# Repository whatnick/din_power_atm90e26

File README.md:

# DIN Rail Format Energy Meter Base Board
## Power SMPS module
- 90v-240v AC input
- Isolated 5V output
- 600mA / 3W power rating

## Over-voltage protection/over-current protection
- 0.1A rated PTC fuse
- 300V rated TVS suppressors, x1 per-phase

## Isolation
- 5v DC-DC isolator to power metering module

## Power supply clean-up
- x2 1117 series LDO for generating 3.3v from 5V input to clean up SMPS noise

## Backup-power
- MCP73831 series floating Lipo battery charger for backup lipo battery

## AC Voltage Sampler
- x3 Voltage divider ladders with 880K + 1K total serial resistance

## AC current Sampler
- x8 2.4ohm current sense resistor based CT clamp inputs

## Connectors
- 5.08mm spacing phoenix contact AC voltage connector
- Molex nanofit 2x4 type dense AC current clamp connectors

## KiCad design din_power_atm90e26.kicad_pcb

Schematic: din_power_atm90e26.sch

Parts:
C1, C2, C3: 33n; C_0603
C4, C5, C6, C7, C8, C9: 1uF; C_0603
D1: D_Schottky; D_SOD-323F
D2: LED; LED_0603
F1: Polyfuse; C_Disc_D10.0mm_W2.5mm_P5.00mm
G1: LOGO; Whatnick_logo
J1: CONN_01X06; PhoenixContact_MC-G_06x5.08mm_Angled
J2: VBAT; JST_SH_BM02B-SRSS-TB_02x1.00mm_Straight
J3, J5: CONN_01X08; Molex_NanoFit_2x04x2.50mm_Angled
J4: CONN_02X18; PCIE-36-SKT
L1: Ferrite_Bead_Small; L_1206
LOGO_OSHW1: Logo_Open_Hardware_Small; OSHW-Symbol_6.7x6mm_SilkScreen
R1, R2, R3, R4, R8, R9, R10, R11, R18, R19, R20, R21, R28, R29, R30, R31: 5.8R; R_0603
R5, R6, R12, R13, R15, R16, R22, R23, R24: 220K; R_1206
R7, R14, R17: R; R_1206
R25, R26, R27: 1K; R_0603
R32: 2K; R_0603
R33: 470R; R_0603
RV1, RV2, RV3: Varistor; SMD-4032
SYM1: SYM_Flash_Small; Fsilk_HV
U1: MCP73831-2-OT; SOT-23-5
U2, U3: AP7365-33YG-13; SOT-89-3
U4: Hi-Link_SMPS; HKLPM01
U5: dc-dc; SIP4

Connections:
+3.3V_ISO: C8.1, J4.8, U3.1 (VO)
+3V3: C7.1, J4.32, U2.1 (VO)
+5V_ISO: C5.1, J4.9, U3.3 (VI), U5.4
/UN_IN: F1.1, U4.2 (AC_N)
/ua_1: R5.1, R12.2
/ua_2: R12.1, R15.2
/ua_3: R15.1, R22.2
/ub_1: R6.1, R13.2
/ub_2: R13.1, R16.2
/ub_3: R16.1, R23.2
/uc_1: R7.1, R14.2
/uc_2: R14.1, R17.2
/uc_3: R17.1, R24.2
GNDA: C1.2, C2.2, C3.2, C5.2, C8.2, J4.7, L1.1, R1.1, R2.2, R3.1, R4.2, R8.1, R9.2, R10.1, R11.2, R18.1, R19.2, R20.1, R21.2, R25.1, R26.1, R27.1, R28.1, R29.2, R30.1, R31.2, U3.2 (GND), U5.3
GNDPWR: C4.2, C6.2, C7.2, C9.1, J2.2, J4.36, R32.2, U1.2 (Vss), U2.2 (GND), U4.3 (-VO), U5.1
IA1+: J4.11, J5.1, R1.2
IA1-: J4.13, J5.2, R2.1
IA2+: J3.1, J4.27, R18.2
IA2-: J3.2, J4.29, R19.1
IB1+: J4.15, J5.3, R8.2
IB1-: J4.17, J5.4, R9.1
IB2+: J3.3, J4.31, R28.2
IB2-: J3.4, J4.33, R29.1
IC1+: J4.19, J5.5, R3.2
IC1-: J4.21, J5.6, R4.1
IC2+: J3.5, J4.35, R20.2
IC2-: J3.6, J4.2, R21.1
IN1+: J4.23, J5.7, R10.2
IN1-: J4.25, J5.8, R11.1
IN2+: J3.7, J4.4, R30.2
IN2-: J3.8, J4.6, R31.1
unnamed: D2.1, R33.1
unnamed: R32.1, U1.5 (PROG)
unnamed: R33.2, U1.1 (STAT)
UA: J1.1, R5.2, RV1.2
UA_SAMP: C3.1, J4.5, R22.1, R25.2
UB: J1.3, R6.2, RV2.2
UB_SAMP: C1.1, J4.3, R23.1, R26.2
UC: J1.5, R7.2, RV3.2, U4.1 (AC_L)
UC_SAMP: C2.1, J4.1, R24.1, R27.2
UN: F1.2, J1.6, L1.2, RV1.1, RV2.1, RV3.1
VBAT: C9.2, D1.2, J2.1, J4.30, U1.3 (Vbat)

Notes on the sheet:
Power Systems (5V)
Voltage Sampling
Current Sampling
CT Input
Connector for Metering/Processor boards - Supplies IV samples and +5V power with/without isolation
Optional N-CT1
Option N-CT2
Power Systems - Battery and 3.3V

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
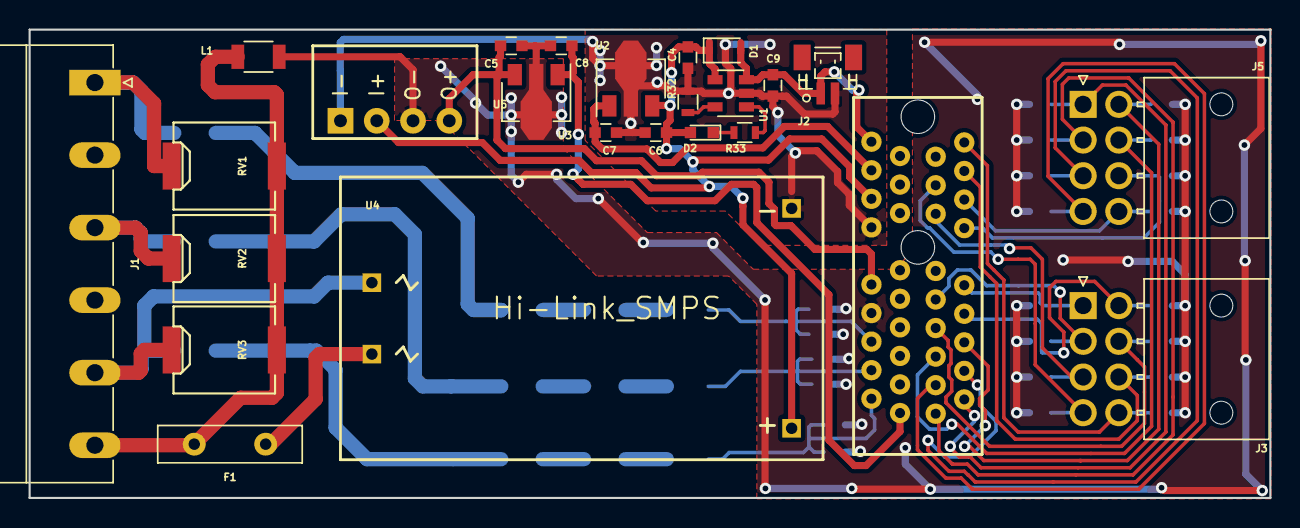
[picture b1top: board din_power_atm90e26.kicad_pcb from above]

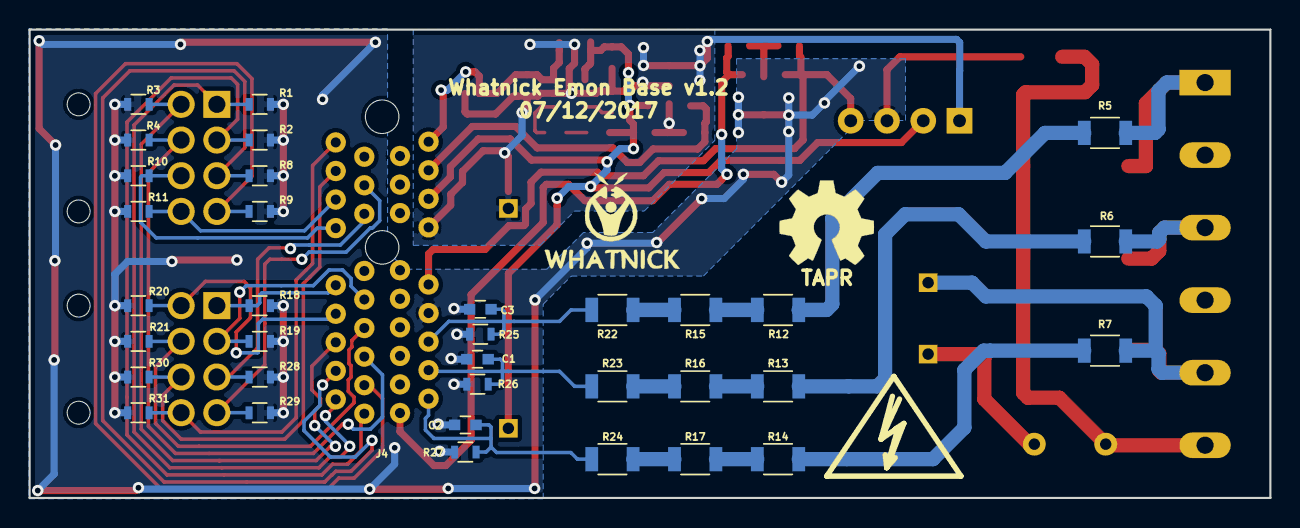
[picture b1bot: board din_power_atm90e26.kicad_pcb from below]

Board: 2 copper layers, 86.9 x 32.8 mm, 62 parts (38 on the bottom side), 43 nets.

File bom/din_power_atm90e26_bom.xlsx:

References | manf# | Value | Footprint | Quantity
C4, C5, C6, C7, C8, C9 | 0603ZD105KAT2A | 1uF | C_0603 | 6
C1, C2, C3 | CC0603KRX7R9BB333 | 33n | C_0603 | 3
R5, R6, R7, R12, R13, R14, R15, R16, R17, R22, R23, R24 | CRCW1206220KFKEA | 220K | R_1206 | 12
R25, R26, R27, R33 | CRG0603F1K0 | 1K | R_0603 | 4
R1, R2, R3, R4, R8, R9, R10, R11, R18, R19, R20, R21, R28, R29, R30, R31 | CRL0603-FW-2R40ELF | 5.8R | R_0603 | 16
R32 | RT0603DRE072KL | 2K | R_0603 | 1
L1 | AIML-1206-R27K-T | Ferrite_Bead_Small | L_1206 | 1
D2 | LTST-C190KRKT | LED | LED_0603 | 1
D1 | PMEG1020EA | D_Schottky | D_SOD-323F | 1
U2, U3 | AP7365-33YG-13 | AP7365-33YG-13 | SOT-89-3 | 2
U4 | HLK-PM01 | Hi-Link_SMPS | HKLPM01 | 1
U1 | MCP73831T-3ACI/OT | MCP73831-2-OT | SOT-23-5 | 1
U5 | ROE-0505S | dc-dc | SIP4 | 1
F1 | 0ZRE0012FF1C | Polyfuse | C_Disc_D10.0mm_W2.5mm_P5.00mm | 1
RV1, RV2, RV3 | VP3225K401R275 | Varistor | SMD-4032 | 3
J4 | 10018784-10210TLF | CONN_02X18 | PCIE-36-SKT | 1
J3, J5 | 1053141108 | CONN_01X08 | Molex_NanoFit_2x04x2.50mm_Angled | 2
J1 | 1759059 | CONN_01X06 | PhoenixContact_MC-G_06x5.08mm_Angled | 1
J2 | BM02B-SRSS-TB(LFSN) | VBAT | JST_SH_BM02B-SRSS-TB_02x1.00mm_Straight | 1

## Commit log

2017-11-04 Initial import laying out parts
2017-11-04 Layout footprints
2017-11-12 Changes from urbito
2017-11-12 DRC change
2017-11-13 Second iteration
2017-11-16 Urbito work 16/11/2017
2017-11-17 Urbito work 17/11/2017
2017-11-18 Urbito delivery 18/11/2017
2017-11-18 Reroute sections, clean up silk screen
2017-11-18 Add OSHW logo
2017-11-18 Save .cmp file
2017-11-22 Generate gerbers
2017-11-22 Add dimensions
2017-11-27 Add more part numbers
2017-12-02 Address issue #1 with changes to schematic component
2017-12-05 New routing from Joslyn address #1
2017-12-05 Moved some parts and bumped version
2017-12-05 Changed 3D models
2017-12-05 New screenshots
2017-12-05 Add new part numbers and high voltage sym
2017-12-07 Small silk screen changes and bump date
2017-12-07 New gerbers
2017-12-25 Update parts to fit Kicost
2018-02-24 Added MSTBA phoenix contact 3D model
2019-02-18 Updated CAD output
2019-02-18 Added README.md
2019-02-18 Remove screenshot
2019-04-16 Remap 3D models
2020-03-18 Port to KiCAD v5.0
2020-03-18 New gerbers and gitignore
2020-03-18 Move BOM and dimension PCB
2020-03-18 New location for BOM
2020-03-19 Generate new gerbers
